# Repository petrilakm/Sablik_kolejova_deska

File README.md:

# sablik kolejova deska

připojení originální kolejové desky k hJOP pro indikace z modelového kolejiště.
Kolejová deska se chová jako virtuální vyhýbky na sběrnici XpressNET

pro komunikaci s XpressNETem je vytvořena knihovna, která komunikuje
s centrálou jako ovladač LH100.

Panel je jednoúčelový

Control panel for railway switch operation via XpressNET (NX)
tested on Lenz LZV100 and Paco's NanoX. Panel send messages same way as hand controller LH100.
Used microcontroller is ATmega328 (Arduino Nano) and SPI communication with 74HC595 and 74HC165 expanders,
but code can be easily deployed to other AVR family controllers.

On XpressNET there is many virtual switches, which are indicated on real outputs.
Control program (hJOP) sets this virtual switches via python API.

This control panel is only for one purpouse. All changes must be done in source code.

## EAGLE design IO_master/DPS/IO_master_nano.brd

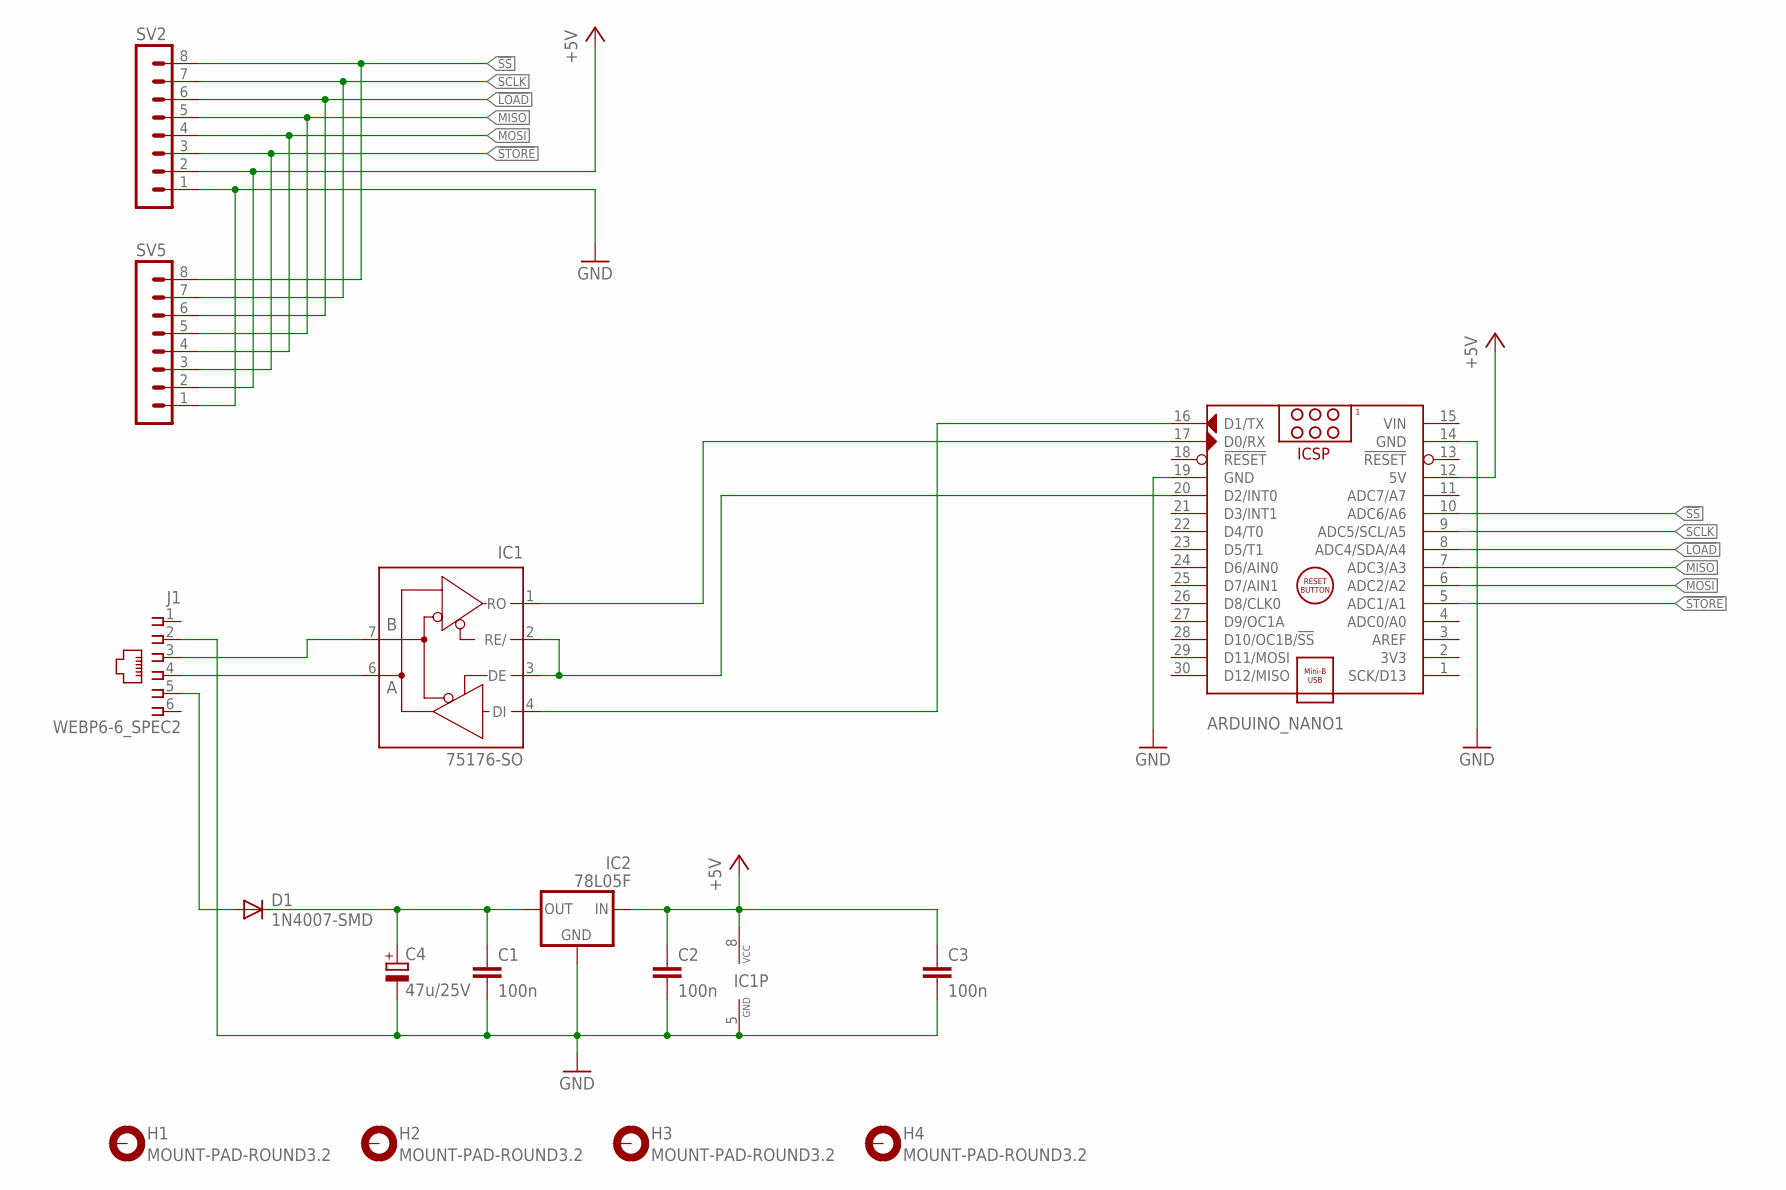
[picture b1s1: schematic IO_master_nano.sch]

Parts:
ARDUINO_NANO1: ARDUINO_NANO_2; ARDUINO_NANO2
C1, C2, C3: 100n; C1206
C4: 47u/25V; E2,5-6L
D1: 1N4007-SMD; SMA-DO214AC
H1, H2, H3, H4: MOUNT-PAD-ROUND3.2; 3,2-PAD
IC1: 75176-SO; SO08
IC2: 78L05F; SOT89
J1: WEBP6-6_SPEC2
SV2, SV5: MA08-1

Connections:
!LOAD: ARDUINO_NANO1.8 (ADC4/SDA/A4), SV2.6, SV5.6
!SS: ARDUINO_NANO1.10 (ADC6/A6), SV2.8, SV5.8
!STORE: ARDUINO_NANO1.5 (ADC1/A1), SV2.3, SV5.3
+5V: ARDUINO_NANO1.12 (5V), C2.1, C3.1, IC1.8 (VCC), IC2.3 (VI), SV2.2, SV5.2
GND: ARDUINO_NANO1.14 (GND), ARDUINO_NANO1.19 (GND), C1.2, C2.2, C3.2, C4.-, IC1.5 (GND), IC2.2 (GND), IC2.2@1 (GND), J1.2, SV2.1, SV5.1
MISO: ARDUINO_NANO1.7 (ADC3/A3), SV2.5, SV5.5
MOSI: ARDUINO_NANO1.6 (ADC2/A2), SV2.4, SV5.4
unnamed: D1.A, J1.5
unnamed: C1.1, C4.+, D1.K (C), IC2.1 (VO)
unnamed: IC1.6 (A), J1.4
unnamed: IC1.7 (B), J1.3
unnamed: ARDUINO_NANO1.20 (D2/INT0), IC1.2 (RE/), IC1.3 (DE)
unnamed: ARDUINO_NANO1.16 (D1/TX), IC1.4 (DI)
unnamed: ARDUINO_NANO1.17 (D0/RX), IC1.1 (RO)
SCLK: ARDUINO_NANO1.9 (ADC5/SCL/A5), SV2.7, SV5.7
VIN: ARDUINO_NANO1.15 (VIN)

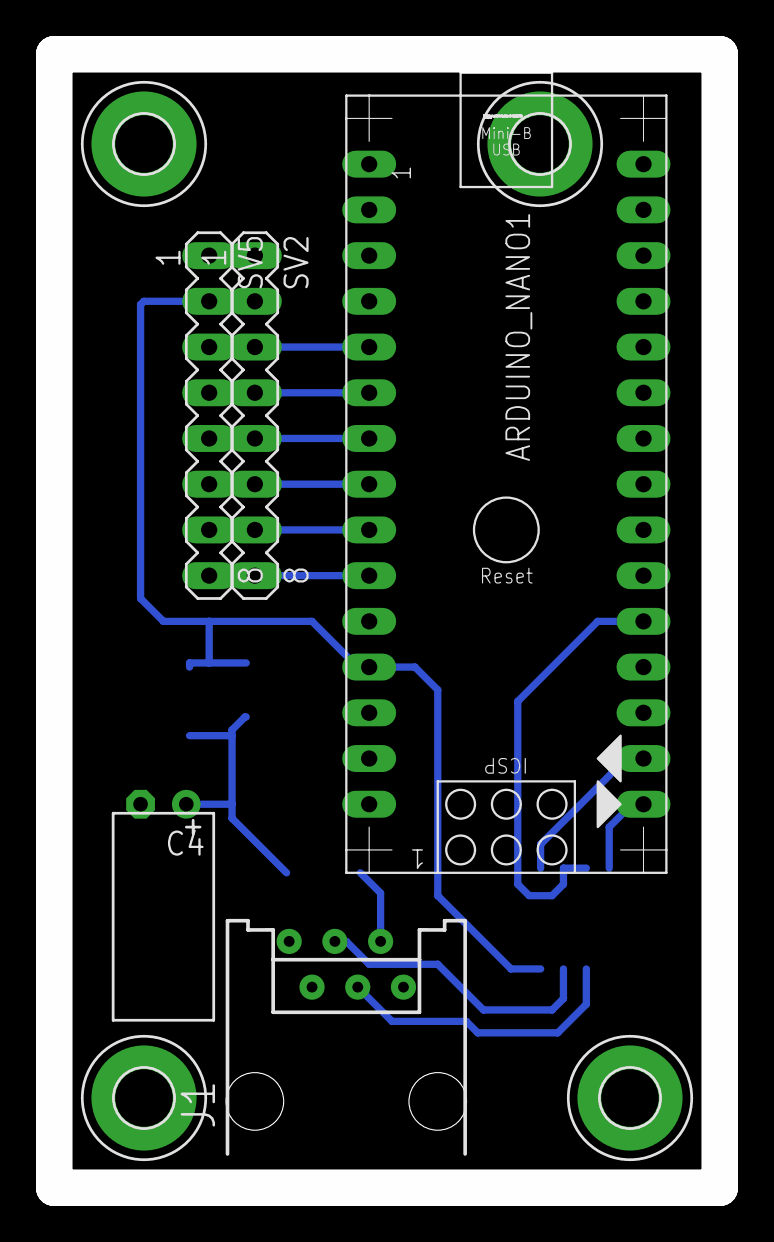
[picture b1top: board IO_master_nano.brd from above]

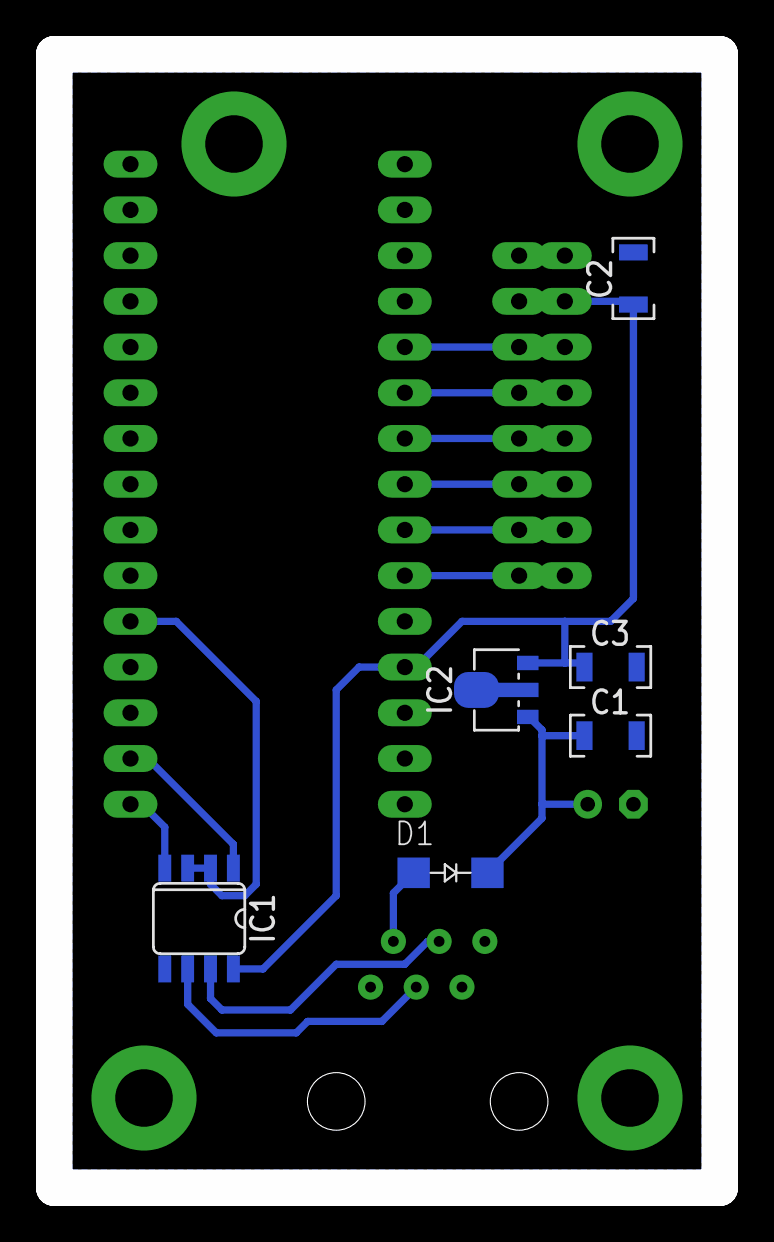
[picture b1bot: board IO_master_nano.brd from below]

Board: 2 copper layers, 37.0 x 63.0 mm, 15 parts (6 on the bottom side), 15 nets.

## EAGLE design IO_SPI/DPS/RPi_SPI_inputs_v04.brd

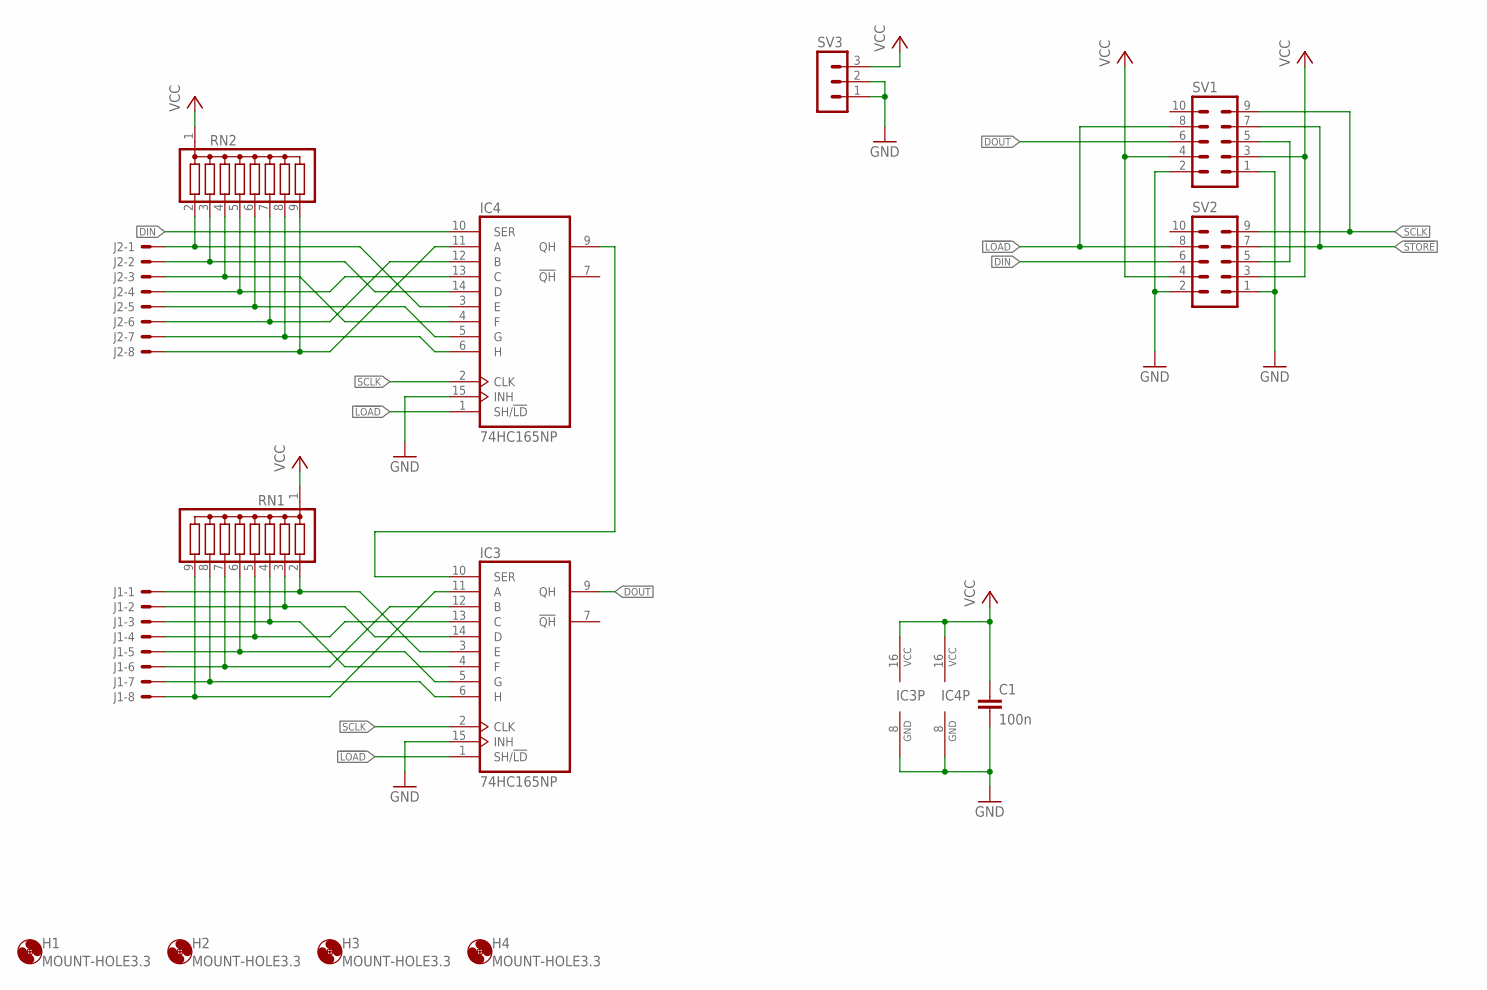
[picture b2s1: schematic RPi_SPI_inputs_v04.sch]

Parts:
C1: 100n; C1206
H1, H2, H3, H4: MOUNT-HOLE3.3; 3,3
IC3, IC4: 74HC165NP; SOCKET-16
J1, J2: 22-05-7088-SPEC-08; 7395-08_SPEC
RN1, RN2: G08R; SIL9
SV1, SV2: ML10
SV3: MA03-1_NO

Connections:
!LOAD: IC3.1 (SH/!LD), IC4.1 (SH/!LD), SV1.8, SV2.8
!STORE: SV1.7, SV2.7
DIN: IC4.10 (SER), SV2.6
DOUT: IC3.9 (QH), SV1.6
DRET: SV1.5, SV2.5
GND: C1.2, IC3.8 (GND), IC3.15 (INH), IC4.8 (GND), IC4.15 (INH), SV1.1, SV1.2, SV2.1, SV2.2, SV3.1, SV3.2
unnamed: IC4.11 (A), J2.8, RN2.9
unnamed: IC4.6 (H), J2.7, RN2.8
unnamed: IC3.10 (SER), IC4.9 (QH)
unnamed: IC4.12 (B), J2.6, RN2.7
unnamed: IC4.5 (G), J2.5, RN2.6
unnamed: IC4.13 (C), J2.4, RN2.5
unnamed: IC4.4 (F), J2.3, RN2.4
unnamed: IC4.14 (D), J2.2, RN2.3
unnamed: IC4.3 (E), J2.1, RN2.2
unnamed: IC3.3 (E), J1.1, RN1.2
unnamed: IC3.14 (D), J1.2, RN1.3
unnamed: IC3.4 (F), J1.3, RN1.4
unnamed: IC3.13 (C), J1.4, RN1.5
unnamed: IC3.5 (G), J1.5, RN1.6
unnamed: IC3.12 (B), J1.6, RN1.7
unnamed: IC3.6 (H), J1.7, RN1.8
unnamed: IC3.11 (A), J1.8, RN1.9
SCLK: IC3.2 (CLK), IC4.2 (CLK), SV1.9, SV2.9
VCC: C1.1, IC3.16 (VCC), IC4.16 (VCC), RN1.1, RN2.1, SV1.3, SV1.4, SV2.3, SV2.4, SV3.3

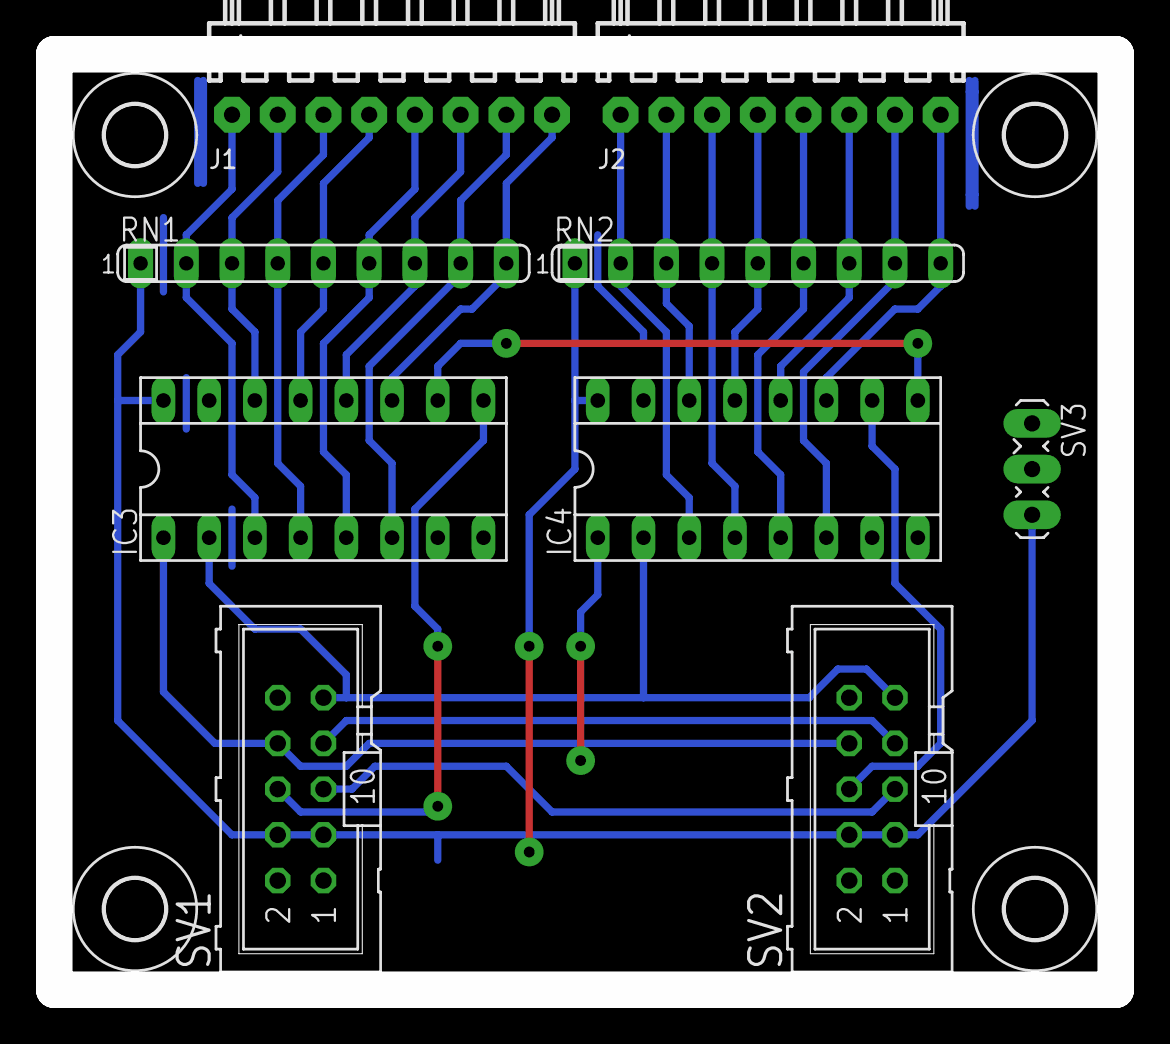
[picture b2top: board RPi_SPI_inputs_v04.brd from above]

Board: 2 copper layers, 59.0 x 52.0 mm, 14 parts (1 on the bottom side), 25 nets.

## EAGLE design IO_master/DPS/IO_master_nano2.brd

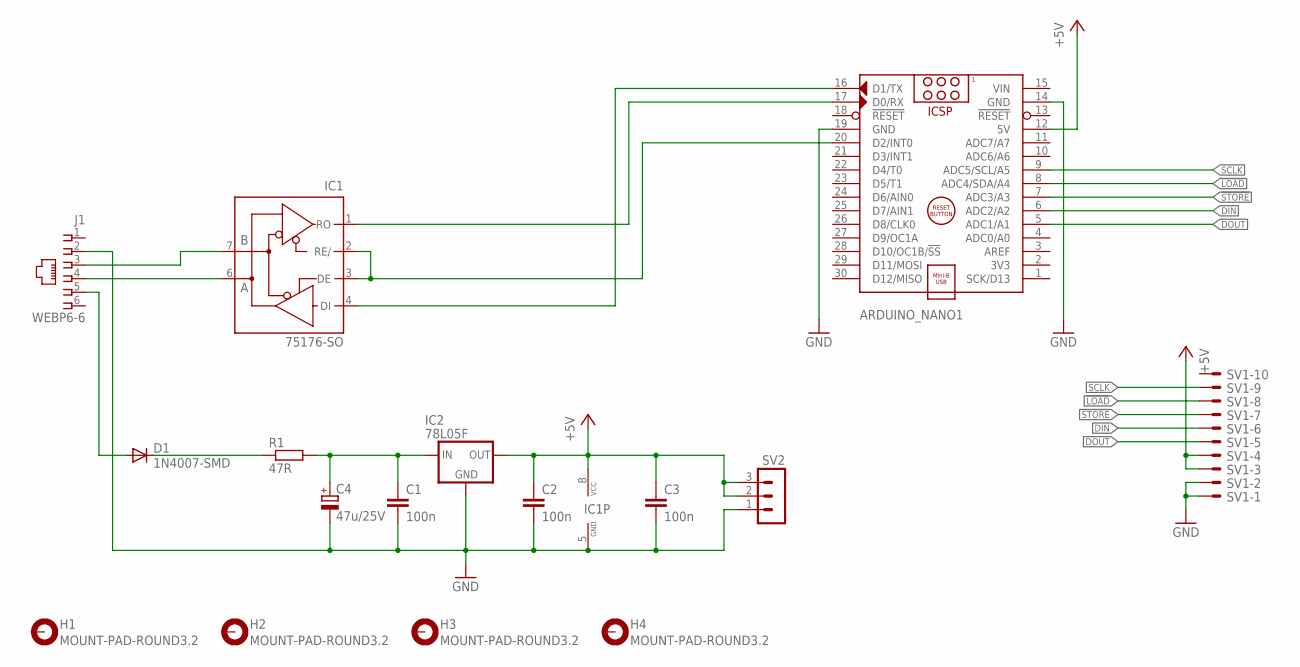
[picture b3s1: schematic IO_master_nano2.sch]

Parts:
ARDUINO_NANO1: ARDUINO_NANO_2; ARDUINO_NANO2
C1, C2, C3: 100n; C1206
C4: 47u/25V; E2,5-7
D1: 1N4007-SMD; SMA-DO214AC
H1, H2, H3, H4: MOUNT-PAD-ROUND3.2; 3,2-PAD
IC1: 75176-SO; SO08
IC2: 78L05F; SOT89
J1: WEBP6-6; WEBP6-6_SPEC2
R1: 47R; 0204/5
SV1: ML10E; ML10
SV2: MA03-1_NO

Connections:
!LOAD: ARDUINO_NANO1.8 (ADC4/SDA/A4), SV1.8
!STORE: ARDUINO_NANO1.7 (ADC3/A3), SV1.7
+5V: ARDUINO_NANO1.12 (5V), C2.1, C3.1, IC1.8 (VCC), IC2.1 (VO), SV1.3, SV1.4, SV2.2, SV2.3
DIN: ARDUINO_NANO1.6 (ADC2/A2), SV1.6
DOUT: ARDUINO_NANO1.5 (ADC1/A1), SV1.5
GND: ARDUINO_NANO1.14 (GND), ARDUINO_NANO1.19 (GND), C1.2, C2.2, C3.2, C4.-, IC1.5 (GND), IC2.2 (GND), IC2.2@1 (GND), J1.2, SV1.1, SV1.2, SV2.1
unnamed: D1.A, J1.5
unnamed: C1.1, C4.+, IC2.3 (VI), R1.2
unnamed: D1.K (C), R1.1
unnamed: IC1.6 (A), J1.4
unnamed: IC1.7 (B), J1.3
unnamed: ARDUINO_NANO1.20 (D2/INT0), IC1.2 (RE/), IC1.3 (DE)
unnamed: ARDUINO_NANO1.16 (D1/TX), IC1.4 (DI)
unnamed: ARDUINO_NANO1.17 (D0/RX), IC1.1 (RO)
SCLK: ARDUINO_NANO1.9 (ADC5/SCL/A5), SV1.9
VIN: ARDUINO_NANO1.15 (VIN)

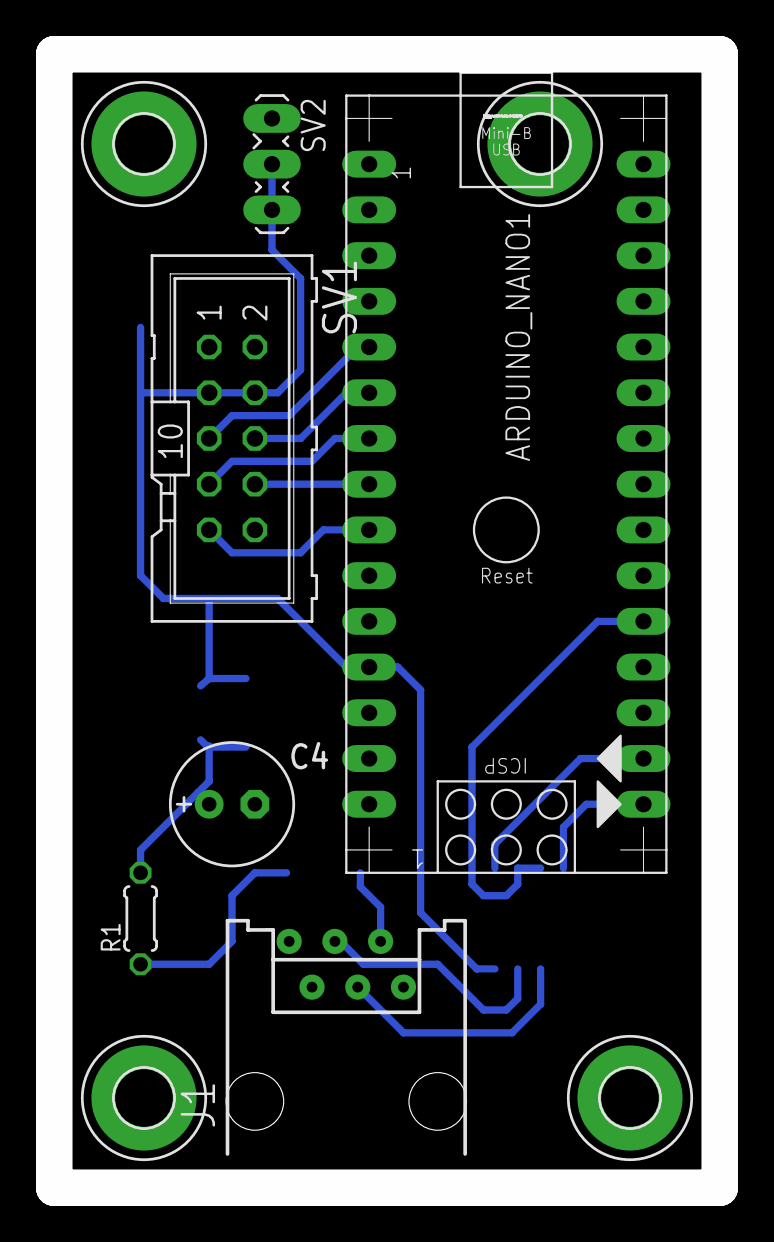
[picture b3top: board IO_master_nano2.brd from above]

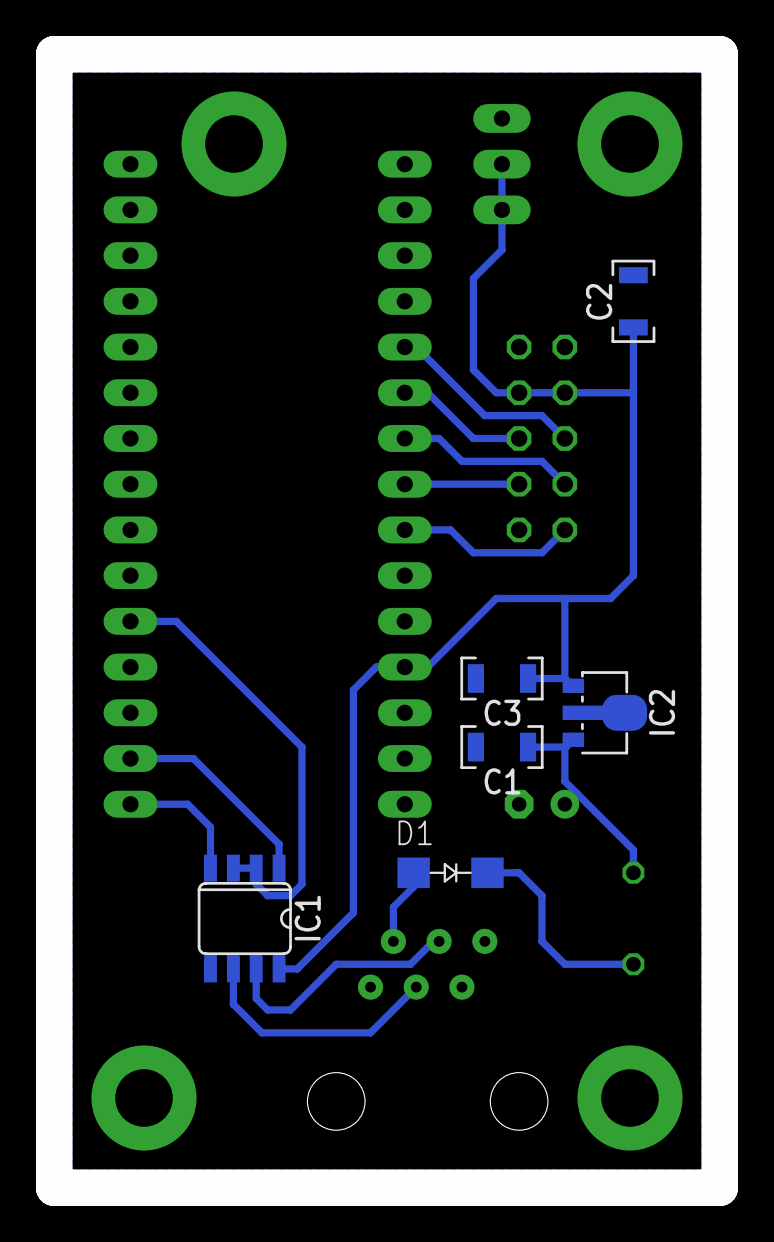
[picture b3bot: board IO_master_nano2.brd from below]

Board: 2 copper layers, 37.0 x 63.0 mm, 16 parts (6 on the bottom side), 15 nets.

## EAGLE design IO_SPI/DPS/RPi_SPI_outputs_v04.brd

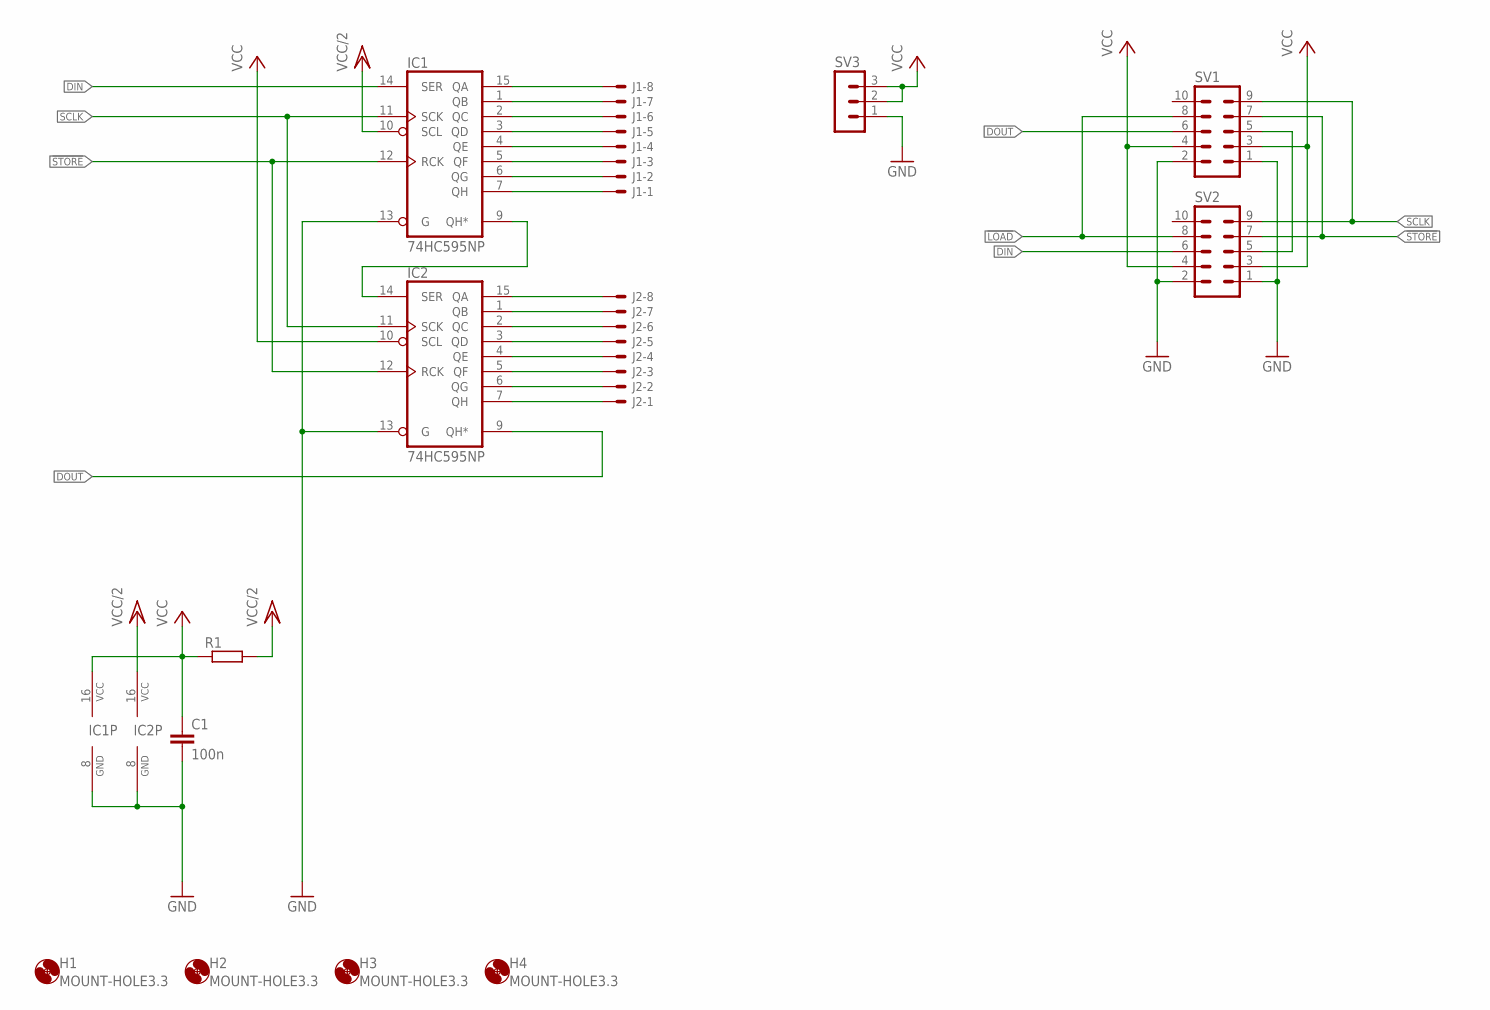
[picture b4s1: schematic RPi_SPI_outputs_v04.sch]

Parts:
C1: 100n; C1206
H1, H2, H3, H4: MOUNT-HOLE3.3; 3,3
IC1, IC2: 74HC595NP; SOCKET-16
J1, J2: 22-05-7088-SPEC-08; 7395-08_SPEC
R1: R-EU_R1206; R1206
SV1, SV2: ML10
SV3: MA03-1_NO

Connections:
!LOAD: SV1.8, SV2.8
!STORE: IC1.12 (RCK), IC2.12 (RCK), SV1.7, SV2.7
DIN: IC1.14 (SER), SV2.6
DOUT: IC2.9 (QH*), SV1.6
DRET: SV1.5, SV2.5
GND: C1.2, IC1.8 (GND), IC1.13 (G), IC2.8 (GND), IC2.13 (G), SV1.1, SV1.2, SV2.1, SV2.2, SV3.1
unnamed: IC1.15 (QA), J1.8
unnamed: IC1.1 (QB), J1.7
unnamed: IC1.2 (QC), J1.6
unnamed: IC1.3 (QD), J1.5
unnamed: IC1.4 (QE), J1.4
unnamed: IC1.5 (QF), J1.3
unnamed: IC1.6 (QG), J1.2
unnamed: IC1.7 (QH), J1.1
unnamed: IC2.15 (QA), J2.8
unnamed: IC2.1 (QB), J2.7
unnamed: IC2.2 (QC), J2.6
unnamed: IC2.3 (QD), J2.5
unnamed: IC2.4 (QE), J2.4
unnamed: IC2.5 (QF), J2.3
unnamed: IC2.6 (QG), J2.2
unnamed: IC2.7 (QH), J2.1
unnamed: IC1.9 (QH*), IC2.14 (SER)
SCLK: IC1.11 (SCK), IC2.11 (SCK), SV1.9, SV2.9
VCC: C1.1, IC1.16 (VCC), IC2.10 (SCL), R1.1, SV1.3, SV1.4, SV2.3, SV2.4, SV3.2, SV3.3
VCC/2: IC1.10 (SCL), IC2.16 (VCC), R1.2

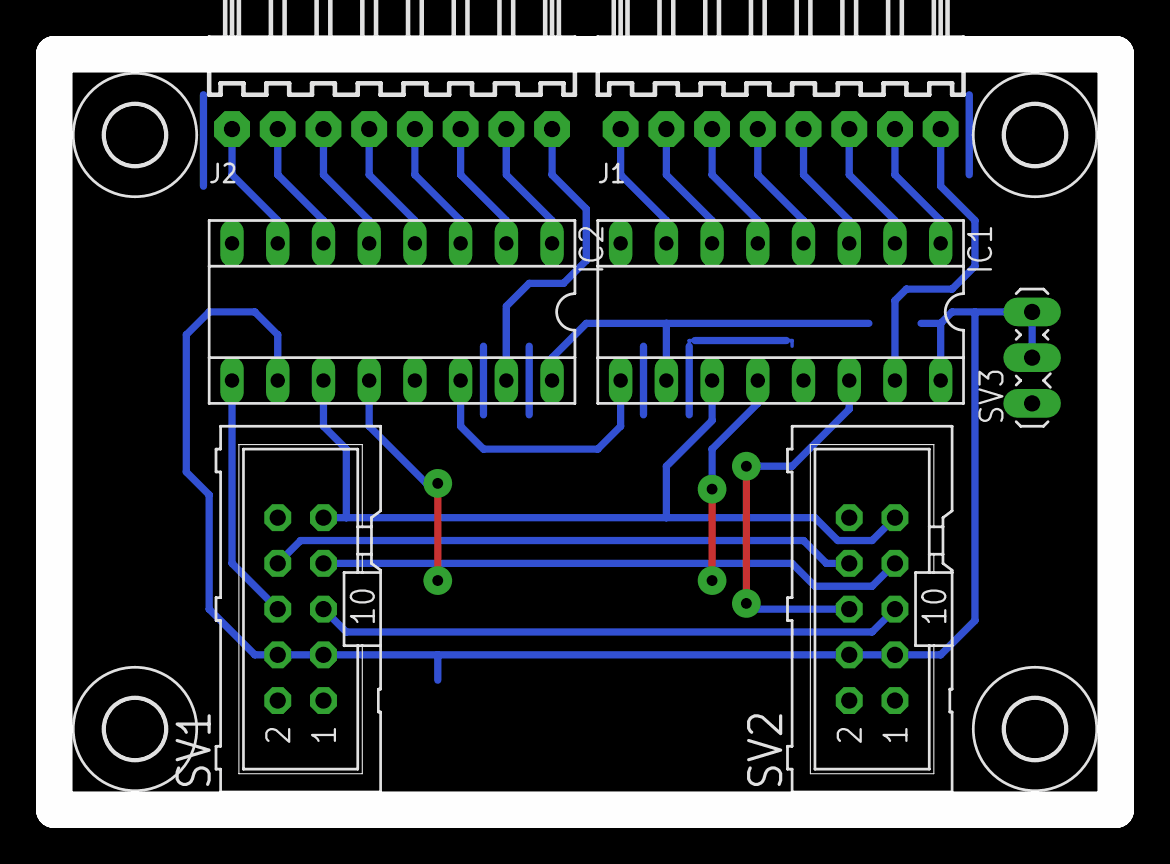
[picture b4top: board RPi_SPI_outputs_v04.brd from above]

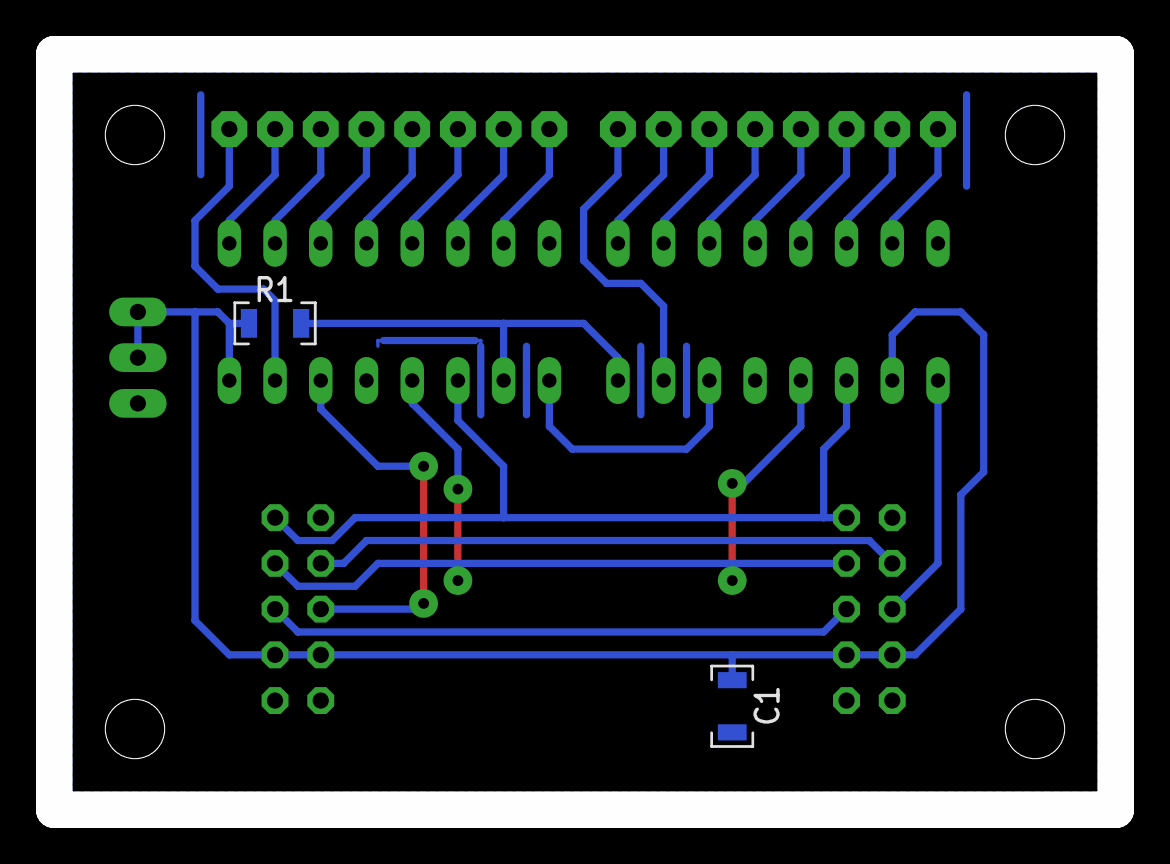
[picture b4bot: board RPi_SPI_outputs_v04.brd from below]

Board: 2 copper layers, 59.0 x 42.0 mm, 13 parts (2 on the bottom side), 26 nets.

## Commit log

2023-04-06 initial commit
    working state
2023-04-06 add LICENSE and README
2023-05-12 aktualni stav, oprava gitignore
2023-05-12 clear code in calculate_output
2023-05-12 inputs mapped to XpressNET addresses 549-558
    RM 138-140
2023-05-14 funkci verze
    vsechny vstupy prirazeny spravne
2023-06-10 Po startu pustit vsechna tlacitka
    A uprava excelu se vestupy/vystupy
2023-06-10 opraveny fuses na funkcni
2023-06-10 oprava dotazu na stavy po spusteni
2023-06-10 oprava nacteni stavu po startu
